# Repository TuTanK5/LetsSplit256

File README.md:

# LetsSplit256
My take on a PCB design for Let's Split with 2x5x6 keys (2 hands, each with 5 rows and 6 columns).

Has both column-staggered and ortholinear layouts.

QMK firmware:

https://github.com/TuTanK5/qmk_firmware/tree/master/keyboards/lets_split_256

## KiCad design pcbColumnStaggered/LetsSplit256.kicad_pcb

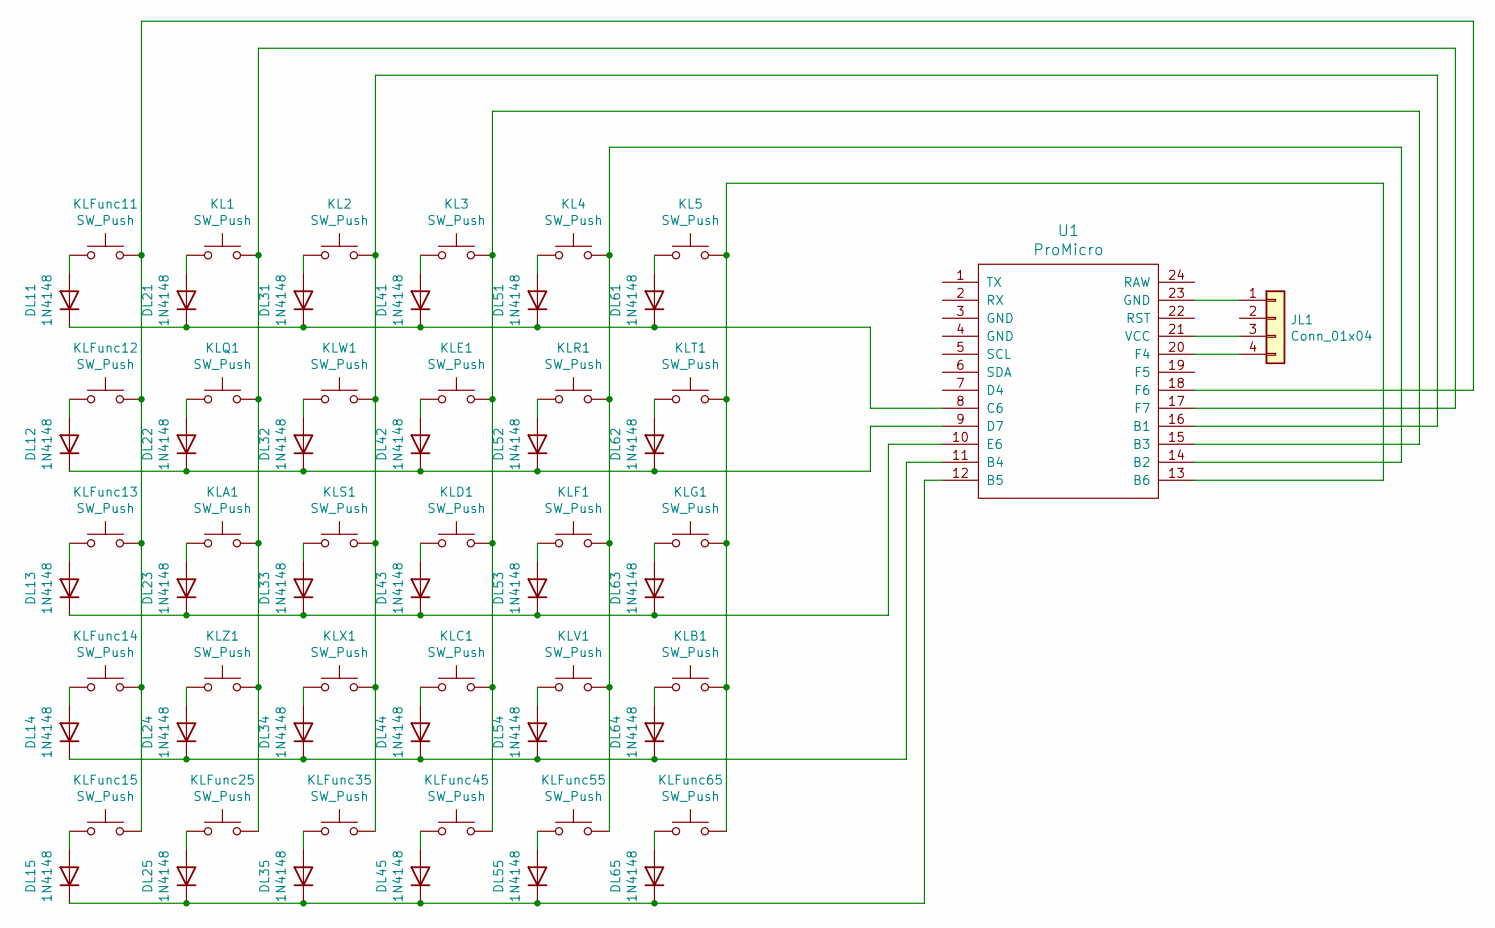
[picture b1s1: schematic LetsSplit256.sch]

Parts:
DL11, DL12, DL13, DL14, DL15, DL21, DL22, DL23, DL24, DL25, DL31, DL32, DL33, DL34, DL35, DL41, DL42, DL43, DL44, DL45, DL51, DL52, DL53, DL54, DL55, DL61, DL62, DL63, DL64, DL65: 1N4148; D_DO-35_SOD27_P7.62mm_Horizontal
JL1: Conn_01x04; PinHeader_1x04_P2.54mm_Horizontal
KL1, KL2, KL3, KL4, KL5: SW_Push; cherry
KLA1: SW_Push; cherry
KLB1: SW_Push; cherry
KLC1: SW_Push; cherry
KLD1: SW_Push; cherry
KLE1: SW_Push; cherry
KLF1: SW_Push; cherry
KLFunc11, KLFunc12, KLFunc13, KLFunc14, KLFunc15, KLFunc25, KLFunc35, KLFunc45, KLFunc55, KLFunc65: SW_Push; cherry
KLG1: SW_Push; cherry
KLQ1: SW_Push; cherry
KLR1: SW_Push; cherry
KLS1: SW_Push; cherry
KLT1: SW_Push; cherry
KLV1: SW_Push; cherry
KLW1: SW_Push; cherry
KLX1: SW_Push; cherry
KLZ1: SW_Push; cherry
U1: ProMicro

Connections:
unnamed: DL11.1 (K), DL21.1 (K), DL31.1 (K), DL41.1 (K), DL51.1 (K), DL61.1 (K), U1.8 (C6)
unnamed: DL11.2 (A), KLFunc11.1
unnamed: DL12.1 (K), DL22.1 (K), DL32.1 (K), DL42.1 (K), DL52.1 (K), DL62.1 (K), U1.9 (D7)
unnamed: DL12.2 (A), KLFunc12.1
unnamed: DL13.1 (K), DL23.1 (K), DL33.1 (K), DL43.1 (K), DL53.1 (K), DL63.1 (K), U1.10 (E6)
unnamed: DL13.2 (A), KLFunc13.1
unnamed: DL14.1 (K), DL24.1 (K), DL34.1 (K), DL44.1 (K), DL54.1 (K), DL64.1 (K), U1.11 (B4)
unnamed: DL14.2 (A), KLFunc14.1
unnamed: DL15.1 (K), DL25.1 (K), DL35.1 (K), DL45.1 (K), DL55.1 (K), DL65.1 (K), U1.12 (B5)
unnamed: DL15.2 (A), KLFunc15.1
unnamed: DL21.2 (A), KL1.1
unnamed: DL22.2 (A), KLQ1.1
unnamed: DL23.2 (A), KLA1.1
unnamed: DL24.2 (A), KLZ1.1
unnamed: DL25.2 (A), KLFunc25.1
unnamed: DL31.2 (A), KL2.1
unnamed: DL32.2 (A), KLW1.1
unnamed: DL33.2 (A), KLS1.1
unnamed: DL34.2 (A), KLX1.1
unnamed: DL35.2 (A), KLFunc35.1
unnamed: DL41.2 (A), KL3.1
unnamed: DL42.2 (A), KLE1.1
unnamed: DL43.2 (A), KLD1.1
unnamed: DL44.2 (A), KLC1.1
unnamed: DL45.2 (A), KLFunc45.1
unnamed: DL51.2 (A), KL4.1
unnamed: DL52.2 (A), KLR1.1
unnamed: DL53.2 (A), KLF1.1
unnamed: DL54.2 (A), KLV1.1
unnamed: DL55.2 (A), KLFunc55.1
unnamed: DL61.2 (A), KL5.1
unnamed: DL62.2 (A), KLT1.1
unnamed: DL63.2 (A), KLG1.1
unnamed: DL64.2 (A), KLB1.1
unnamed: DL65.2 (A), KLFunc65.1
unnamed: JL1.1, U1.23 (GND)
unnamed: JL1.3, U1.21 (VCC)
unnamed: JL1.4, U1.20 (F4)
unnamed: KL1.2, KLA1.2, KLFunc25.2, KLQ1.2, KLZ1.2, U1.17 (F7)
unnamed: KL2.2, KLFunc35.2, KLS1.2, KLW1.2, KLX1.2, U1.16 (B1)
unnamed: KL3.2, KLC1.2, KLD1.2, KLE1.2, KLFunc45.2, U1.15 (B3)
unnamed: KL4.2, KLF1.2, KLFunc55.2, KLR1.2, KLV1.2, U1.14 (B2)
unnamed: KL5.2, KLB1.2, KLFunc65.2, KLG1.2, KLT1.2, U1.13 (B6)
unnamed: KLFunc11.2, KLFunc12.2, KLFunc13.2, KLFunc14.2, KLFunc15.2, U1.18 (F6)

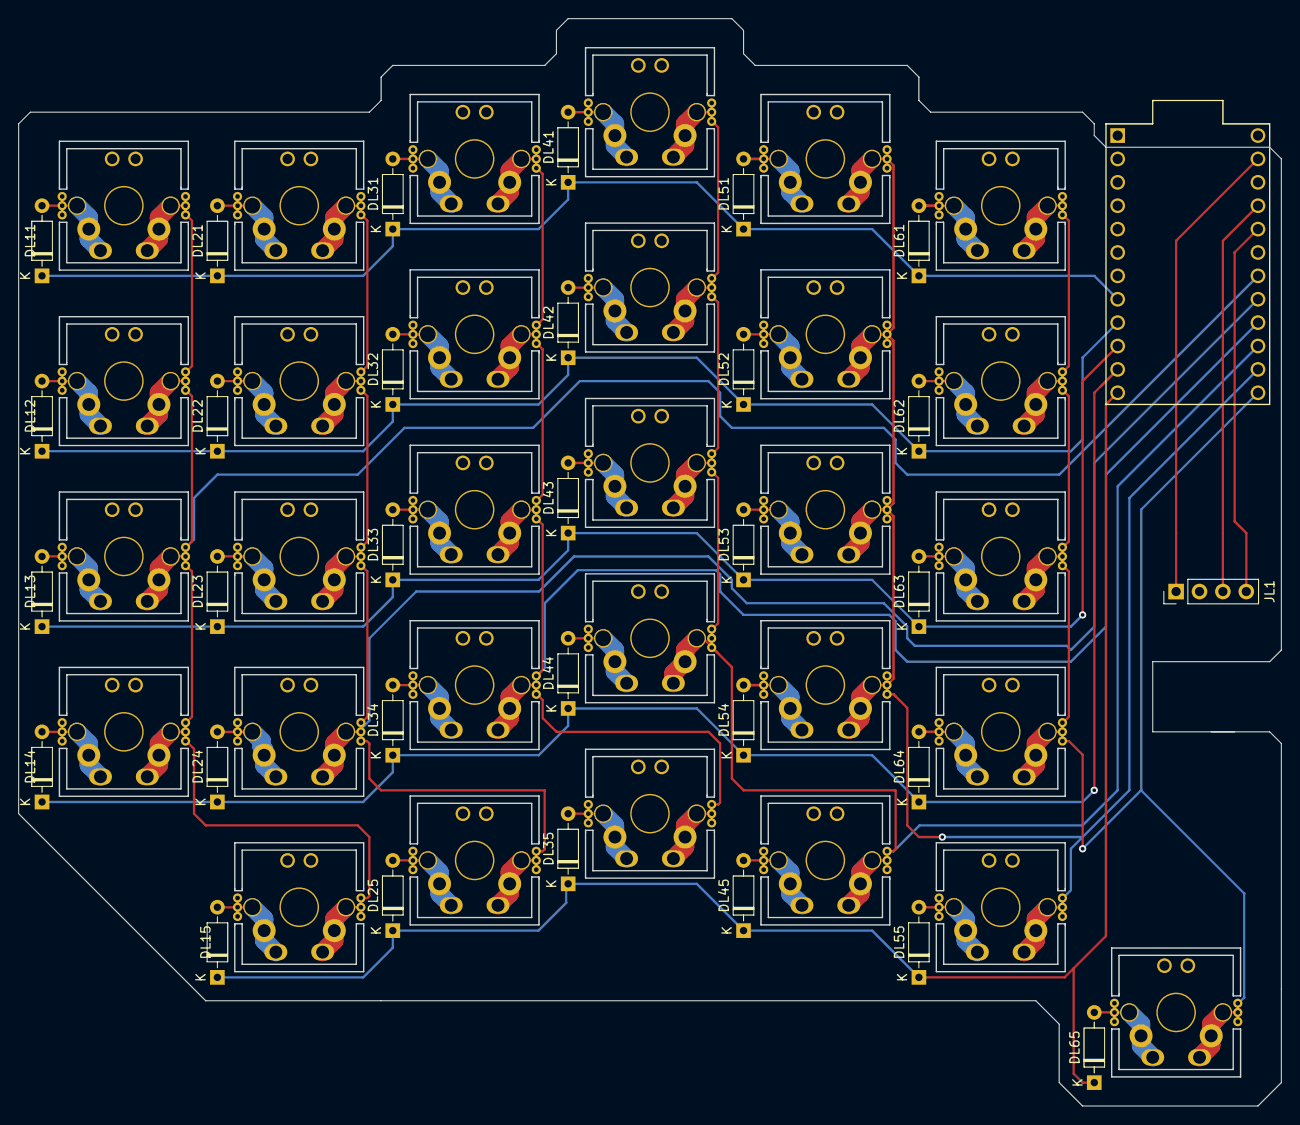
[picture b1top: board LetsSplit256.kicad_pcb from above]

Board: 2 copper layers, 137.1 x 118.0 mm, 62 parts (0 on the bottom side), 44 nets.

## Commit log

2021-03-14 Initial - Left half schematic
2021-03-16 Add footprints for switch and pro micro
2021-03-17 Routing
2021-03-19 Finialize ortho pcb
2021-03-19 Finalize column staggered version
2021-03-21 Update Column Staggered PCB
2021-03-27 Generate geber
2021-04-06 Update BOM
2021-04-06 Update format
2021-04-06 Edit
2021-04-07 Update switch price
2022-01-22 Remove unnecessary jumpers for 3.5mm ports
2022-01-22 Remove redundant files
2022-02-26 Upload image of 3.5mm port used
2024-11-27 notes
